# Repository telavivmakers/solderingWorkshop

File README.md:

# solderingWorkshop
TAMI soldering workshop board designs code and instructions

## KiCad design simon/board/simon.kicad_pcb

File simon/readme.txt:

kicad files go to Board folder
arduino sketches goes to code

compiled HEX goes there as well, we are working with tami attiny85 programmer (link here)

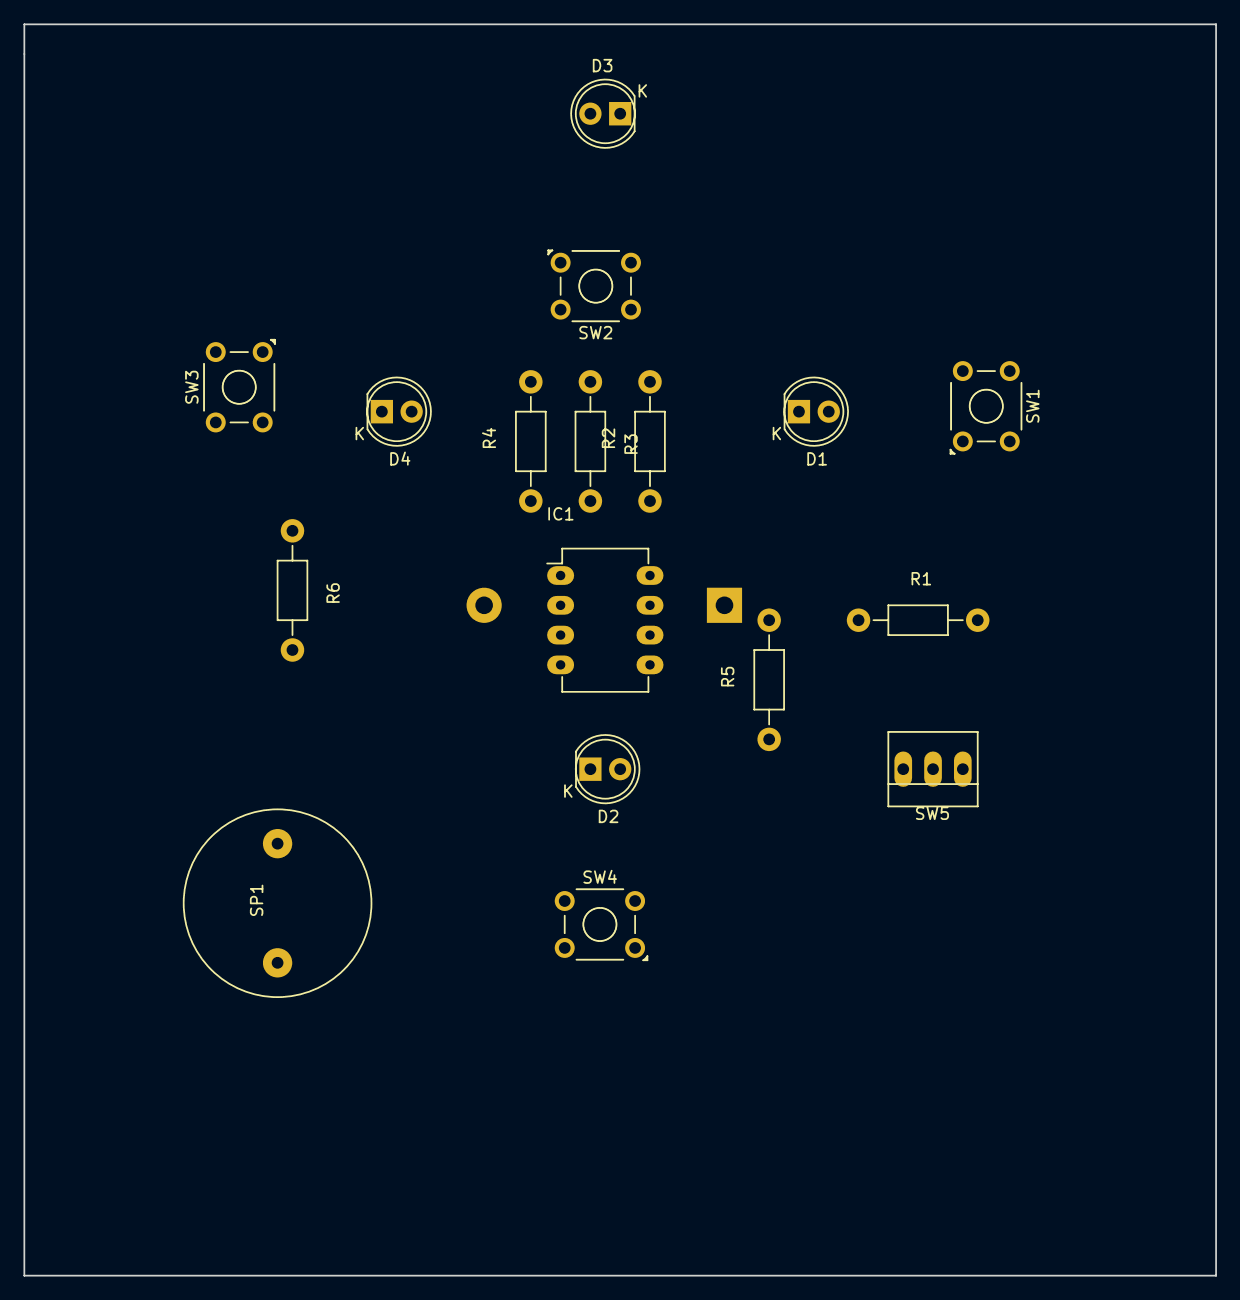
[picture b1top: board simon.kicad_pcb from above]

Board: 2 copper layers, 101.6 x 106.7 mm, 18 parts (1 on the bottom side), 13 nets, no tracks yet.

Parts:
BT1: Battery; Keystone_104_1x23mm-CoinCell
D1, D2, D3, D4: LED; LED-5MM
IC1: ATTINY85-S; DIP-8_W7.62mm_LongPads
R1: 2K; Resistor_Horizontal_RM10mm
R2, R5, R6: 330R; Resistor_Horizontal_RM10mm
R3: 620R; Resistor_Horizontal_RM10mm
R4: 1K; Resistor_Horizontal_RM10mm
SP1: SPEAKER; BUZZER
SW1, SW2, SW3, SW4: button; SW_TH_Tactile_Omron_B3F-10xx
SW5: on/off; PINHEAD1-3

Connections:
+3V3: IC1.8, R1.2, SW5.1
GND: BT1.2, IC1.4, SP1.1, SW1.2, SW2.2, SW3.2, SW4.2
unnamed: BT1.1, SW5.2
unnamed: D1.2, D2.1, R5.1
unnamed: D3.2, D4.1, R6.1
unnamed: R2.1, R3.2, SW2.1
unnamed: R3.1, R4.2, SW3.1
unnamed: R4.1, SW4.1
PB0: IC1.5, R1.1, R2.2, SW1.1
PB1: IC1.6, R5.2
PB2: D1.1, D2.2, IC1.7, R6.2
PB3: D3.1, D4.2, IC1.2
PB4: IC1.3, SP1.2

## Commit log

2016-11-29 schema kicad
2016-11-29 readme
2016-11-29 schmeatic button fix
2016-11-30 Typo police
2016-11-30 added routing single layer
2016-12-03 add code
2016-12-05 boad layout
2016-12-05 added Hex
2016-12-05 removed some board svg floff
